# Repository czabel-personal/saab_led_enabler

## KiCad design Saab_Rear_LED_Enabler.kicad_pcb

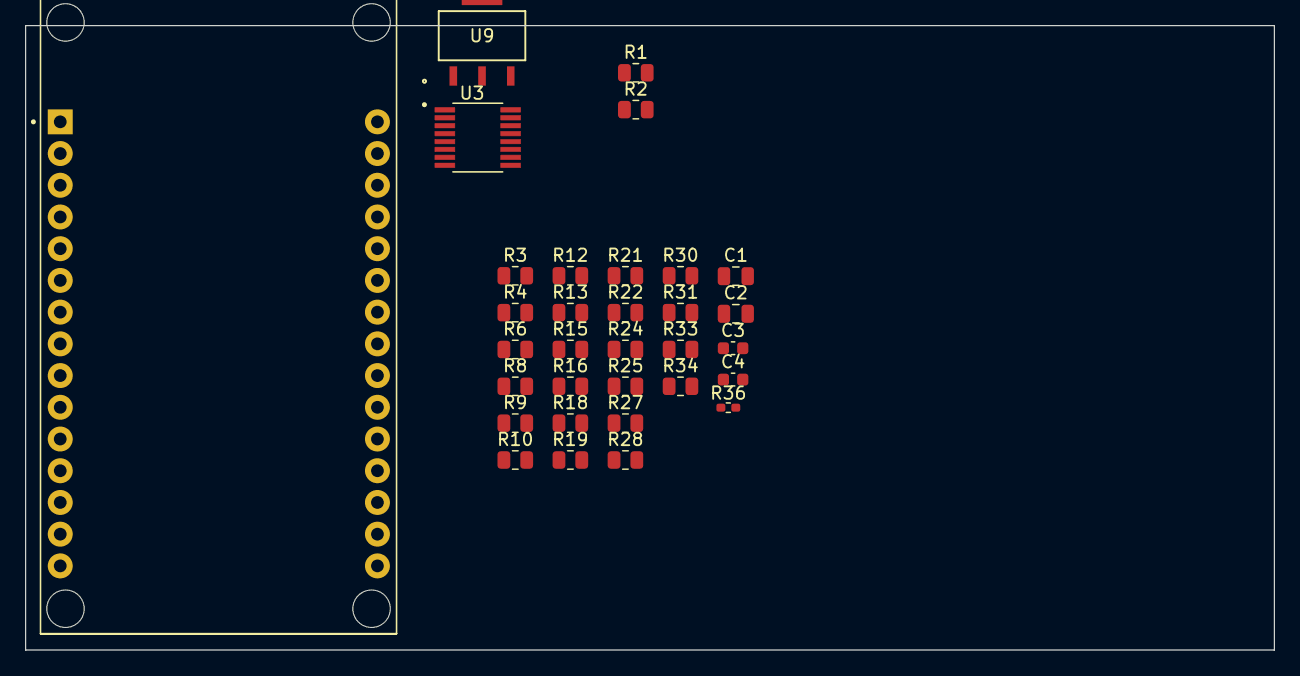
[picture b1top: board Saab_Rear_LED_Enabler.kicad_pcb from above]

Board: 2 copper layers, 100.0 x 50.0 mm, 32 parts (0 on the bottom side), 19 nets, no tracks yet.

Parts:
C1, C2: 10u; C_0805_2012Metric
C3, C4: 0.1u; C_0603_1608Metric
R1, R2: 2.4k; R_0805_2012Metric
R3, R6, R9, R12, R15, R18, R21, R25, R28, R31, R34: 1.5k; R_0805_2012Metric
R4, R8, R10, R13, R16, R19, R22, R24, R27, R30, R33: 150; R_0805_2012Metric
R36: 2k; R_0402_1005Metric_Pad0.72x0.64mm_HandSolder
U1: ESP32-DEVKIT-V1; ESP32_DEVKIT_V1_30PIN
U3: MAX11611EEET; SOP63P602X175-16N
U9: NCP1117ST50T3G; SOT223-3_ONS

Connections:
+12V: C1.1, U9.3 (IN)
/3V3: C3.1, R1.1, R2.1, U1.1 (3V3), U3.16 (VDD)
/5V: C2.1, U1.30 (VIN), U9.2 (OUT)
/AIN0: R3.1, R4.1, U3.5 (AIN0)
/AIN1: R6.1, R8.1, U3.6 (AIN1)
/AIN2: R9.1, R10.1, U3.7 (AIN2)
/AIN3: R12.1, R13.1, U3.8 (AIN3)
/AIN4: R15.1, R16.1, U3.9 (AIN4)
/AIN5: R18.1, R19.1, U3.10 (AIN5)
/AIN6: R21.1, R22.1, U3.11 (AIN6)
/AIN7: R24.1, R25.1, U3.12 (AIN7)
/AIN8: R27.1, R28.1, U3.4 (AIN8)
/AIN9: R30.1, R31.1, U3.3 (AIN9)
/AIN10: R33.1, R34.1, U3.2 (AIN10)
/SCL: R2.2, U1.14 (D22), U3.13 (SCL)
/SDA: R1.2, U1.11 (D21), U3.14 (SDA)
GND: C1.2, C2.2, C3.2, C4.2, R4.2, R8.2, R10.2, R13.2, R16.2, R19.2, R22.2, R24.2, R27.2, R30.2, R33.2, U1.2 (GND), U1.29 (GND), U3.15 (GND), U9.1 (ADJ/GND)
unnamed: C4.1, R36.2
unnamed: R36.1, U3.1 (AIN11/REF)

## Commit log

2024-01-18 Initial commit of work in progress. Current setup is multithreaded, with plans to run a basic webserver on a soft AP setup for UI. LED enablement is currently set up for a single channel only for tes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
2024-01-19 Version 0.60, see Changelog for details
2024-01-20 Revert "Version 0.60, see Changelog for details"
    This reverts commit bf9679f0cda6752c61afaee5e178b03e39d667ae.
2024-01-21 Version 0.70, see changelog for details
2024-02-02 LED Enabler updated to v0.80, see Changelog for details
2024-02-04 Saab LED Enabler is now the name Fixing CALIBRATION if/else block
2024-02-04 No real change, just Github being weird
2024-03-23 Arduino code updated to v0.80, ADC reading now works. See changelog for full details.
